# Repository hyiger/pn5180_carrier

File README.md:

# PN5180 8-Bay NFC Reader Carrier

Carrier board that lets 4 or 8 PN5180 breakout modules plug in over ~30 cm cables with
Molex CLIK-Mate 1.50 mm dual-row (2×5) positive-lock connectors (CLIK-Mate is the white
latching family used on the Prusa LoveBoard) and share one SPI bus with a Seeed Studio
XIAO ESP32C6 soldered flat at the top centre of the board. It runs from the printer's 24 V supply through an MP1584EN buck
module soldered flat onto the carrier. Every part is SMD except the buck module's four
through-hole pads; the XIAO is soldered flat by its castellations. A 74HC138 decodes
3 address lines into the 8 chip selects; a 74HC151 muxes the 8 BUSY lines back to a
single GPIO. The PN5180's IRQ pin is not used — BUSY is the only handshake the SPI
protocol needs.

**GPIO cost: 9 of the XIAO's 11 pins** — SCK, MOSI, MISO, A0, A1, A2, /EN, BUSY, /RST.
D6 and D7 are spare.

Author: hyiger · Rev 1.4 · KiCad 10 files (saved with 10.0.6; KiCad 9 and older cannot open them)

## Files

| File | Purpose |
|---|---|
| `pn5180_carrier.kicad_pro` | Project file — open this in KiCad 10 |
| `pn5180_carrier.kicad_sch` | Schematic (single A3 sheet, all symbols embedded) |
| `pn5180_carrier.kicad_pcb` | 2-layer PCB, 62.5 × 106.5 mm. Layout in progress: J1–J8 now carry the 2×5 503148-1090 footprints (swapped 2026-09-05) but their tracks still need re-routing; a few other nets unrouted; mounting holes not yet placed. All 35 footprints reference a 3D model |
| `carrier.kicad_sym` + `sym-lib-table` | Project-local symbol library (same symbols, for editing) |
| `carrier.pretty/` + `fp-lib-table` | Project-local footprints: the XIAO castellated SMD pattern (plus the older 2×7-socket version, geometry from Seeed's OPL library), the MP1584EN module pads, the CLIK-Mate 503148-1090 2×5 receptacle (from Molex's catalog drawing — KiCad ships no dual-row CLIK-Mate footprint), and copies of the stock 502494-0270 (J10) and NANO2 (F1) footprints that differ only in pointing at a project 3D model |
| `pn5180_carrier_schematic.pdf` / `.png` | Rendered schematic, no KiCad needed |
| `pn5180_carrier_bom.csv` | Full BOM: refs, qty, MPN, Mouser #, footprint, DNP flag |
| `pn5180_carrier_mouser_order.csv` | One-board order list for Mouser's BOM tool (populated parts and cable-side parts with spare terminals) |
| `gerbers/`, `gerbers.zip` | Preview gerber/drill export of the unfinished layout, still with the 1×10 connectors — not a fab package |
| `check_netlist.py` | Asserts the exported netlist against the intended connectivity (`kicad-cli sch export netlist --format kicadsexpr -o net.txt pn5180_carrier.kicad_sch`, then `python3 check_netlist.py net.txt`) |
| `gen_kicad.py` | Historical generator that produced the schematic, symbol library, footprints and BOM through rev 1.3 (KiCad 7 format). The KiCad files have been hand-edited since and are authoritative — don't re-run it over them |
| `CLAUDE.md`, `MEMORY.md` | Design guide and decision log: verified part data, layout state, ERC/DRC baseline, open items |
| `.gitignore` | Keeps KiCad's transient files (`.history/`, `.kicad_prl`, lock files), kicad-cli check outputs and `renders/` out of git |
| `carrier.3dshapes/` | Simplified VRML 3D models (boxes with the right envelopes and colours) for the parts KiCad ships no model for: the 2×5 and 1×2 CLIK-Mate receptacles, the XIAO (flat, plus a socketed variant), the MP1584EN module (black no-trimmer type), the NANO2 fuse. Generated by `tools/gen_3d_models.py`; drop in vendor STEP files when you have them |
| `tools/` | `gen_clikmate_2x5_fp.py` (the 503148-1090 footprint), `gen_xiao_smd_fp.py` (the XIAO castellated footprint), `gen_3d_models.py` (the models above), `render_3d_preview.py` (top, isometric and close-up PNGs of the board via `kicad-cli pcb render`; run with KiCad's bundled Python) |
| `pn5180_carrier_3d_preview.png` | Rendered 3D view of the board with those models |

Footprints reference the stock KiCad libraries and every name was verified against
the 10.0 library set (`Capacitor_SMD`, `Diode_SMD`, `Package_SO`, `Resistor_SMD`, …). If a newer
library renames one, reassign it in the footprint tool — nothing in the netlist
depends on the footprint. Command-line checks use KiCad's `kicad-cli`: `sch erc`,
`pcb drc --schematic-parity`, and `sch export netlist` followed by `check_netlist.py`.

## Connector pinouts

### J1–J8: bay connectors (Molex 503148-1090, CLIK-Mate 1.50 mm 2×5 dual-row right-angle SMT)

Build cables by Molex circuit number: cavity *n* of the 503149-1000 housing is signal *n*,
and signals 1–9 follow the first nine positions of the common red PN5180 module's header,
so the module end is a straight 1-to-9 run plus the second GND (cavity 10 into the same
module GND as cavity 9). Molex's catalog drawings number the two rows as stacked pairs —
odd circuits (1, 3, 5, 7, 9) in one row, even (2, 4, 6, 8, 10) in the other — which puts
5V over 3V3, /RST over NSS, MOSI over MISO, SCK over BUSY and the two GNDs in the last
column. That pairing and the receptacle's lead order are read off the drawings rather than
dimensioned, so before crimping the first cable confirm on Molex's 503149/503148 sales
drawings which end is circuit 1 (and from which face the drawing looks), which row carries
the odd circuits, and the 502579 terminal's insertion orientation. On the PCB the
receptacle's ten leads come out in one 0.75 mm-pitch line, numbered 1 to 10 from the pin-1
end (chamfer and triangle on the footprint), offset half a pitch toward pin 10 because the
even-row tails jog sideways. Pin 10 is a second GND: run it as a separate wire twisted with
SCK and crimp both returns into the module's GND at the far end, which tightens the SCK
return loop over the 30 cm. Verify the module's header order before building cables.

| Pin | Signal | Notes |
|---|---|---|
| 1 | 5V | From carrier 5V rail (module TVDD / RF power) |
| 2 | 3V3 | From the carrier LDO (U4), direct |
| 3 | /RST | Shared by all bays |
| 4 | NSS | Bay-specific, from 74HC138 output *n* |
| 5 | MOSI | Shared |
| 6 | MISO | Shared (module tri-states when NSS high) |
| 7 | SCK | Shared |
| 8 | BUSY | Bay-specific, to 74HC151 input *n*, 100k pull-down (RN1/RN2) |
| 9 | GND | |
| 10 | GND | Second return — twist with SCK in the harness |

Bay *n* ↔ J(n+1) ↔ 74HC138 Y*n* ↔ 74HC151 D*n*. Bay 0 is address 000, bay 7 is 111.

Most PN5180 modules expect both 5 V and 3.3 V supplied (3.3 V for VBAT/PVDD, 5 V for the
RF stage), so the carrier feeds both. If your modules regulate 3.3 V onboard and drive
that pin as an *output*, leave pin 2 out of the cable rather than paralleling two LDOs.

### U5: Seeed XIAO ESP32C6, soldered flat on castellated pads

Pin numbers follow Seeed's own symbol/footprint: 1–11 = D0–D10, 12 = 3V3 out, 13 = GND,
14 = 5V (USB VBUS). Pins 1 (D0) and 14 (5V) are at the USB end. The footprint
(`carrier:Seeed_XIAO_ESP32C6_SMD`) puts 14 SMD pads of 1.5 × 2.5 mm under the module's
castellations (2.54 mm pitch, rows 17.8 mm apart, extending 1.25 mm past the module edge
for the fillet) and carries the 21 × 17.8 mm outline, the USB-C overhang and an antenna
marker — place the XIAO with the USB end at the carrier's top edge and the antenna end
inboard, and keep copper off both layers under the antenna end. The socketed alternative
(`Seeed_XIAO_2x7_Socket`, two Würth 61300711821 1×7 headers) stays in the library.

| Signal | XIAO pin | Symbol pin | GPIO* | Note |
|---|---|---|---|---|
| SCK | D8 | 9 | 19 | hardware SPI SCK, via R6 33 Ω |
| MISO | D9 | 10 | 20 | hardware SPI MISO |
| MOSI | D10 | 11 | 18 | hardware SPI MOSI, via R7 33 Ω |
| /EN | D3 | 4 | 21 | → 74HC138 /E1 (acts as NSS) |
| A0 | D0 | 1 | 0 | |
| A1 | D1 | 2 | 1 | |
| A2 | D2 | 3 | 2 | |
| BUSY | D4 | 5 | 22 | 74HC151 output (I²C SDA pin, unused as such) |
| /RST | D5 | 6 | 23 | shared reset to all bays |
| spare | D6 | 7 | 16 | NC (UART0 TX) |
| spare | D7 | 8 | 17 | NC (UART0 RX) |
| 3V3 out | — | 12 | | NC — the carrier has its own 3V3 LDO |
| GND | — | 13 | | |
| 5V | — | 14 | | from carrier 5V through D1 |

\* GPIO numbers per Seeed's pin diagram; write firmware with the `D0…D10` names from the
board's `pins_arduino.h` and they can't be wrong. `SPI.begin()` with no arguments uses
D8/D9/D10.

**Power path:** Seeed states the XIAO's 5V pin is the raw USB VBUS and that an external
supply must go through a diode. D1 (PMEG2010AEH, 0.3 V drop at our current) does that, so
USB can stay plugged in for flashing while the carrier is powered — neither source can
push into the other. The XIAO's own LDO makes its 3.3 V from ~4.7 V; that's fine. With the
carrier unpowered, USB alone runs the XIAO and D1 keeps VBUS out of the carrier's 5 V rail.

### J10: 24 V input (Molex 502494-0270, CLIK-Mate 2.00 mm 1×2 right-angle SMT)

| Pin | Signal |
|---|---|
| 1 | +24 V from the printer PSU |
| 2 | GND (printer PSU return) |

**Tapping the Core One.** Take it from the PSU's 24 V output terminals — put a crimped
fork/spade terminal under the existing screw next to the xBuddy's lead, positive and
return together, 22 AWG is plenty. Check polarity with a meter before you plug the
carrier in; the connector is keyed but the PSU end isn't. Load is ≤ ~0.4 A at 24 V worst
case (the module's 1.5 A limit at 5 V), typically well under that, so the PSU's headroom
is not a concern. The xBuddy's MMU port also carries firmware-switched 24 V, but it's only
enabled when an MMU is configured, so the PSU terminals are the practical tap.

**Input stage (all on the carrier):** F1 1 A (NANO2 451/453, fast-acting — see open item 13) → D2 SMAJ28A TVS (clamps motor
regen spikes; a reversed input forward-biases it and blows F1) → D3 PMEG6030EP reverse
Schottky (keeps the reversed input off C8/C9 and the module; F1 still blows through D2,
so replace it after fixing the miswire) → C8/C9 2 × 10 µF 50 V → U6.

**Buck (U6): MP1584EN mini module, mounted flat.** The footprint has four 3 mm
through-hole pads on the module's 18.54 × 8.13 mm pad rectangle; lay the module on the
carrier and solder down through its own plated holes, or stand it on four header-pin
stubs — both work on the same pads. IN pads at the "IN" silk end, OUT at "OUT", "+" marks
the top row. Module pad labels vary between makers, so check the module's own silkscreen
against the footprint before soldering.

Three things about this module on a 24 V rail:

- It's rated 28 V max. The TVS (28 V standoff, clamping from ~31 V) and C8/C9 are what
  keep spikes off it — don't leave them out to save parts.
- It's the **fixed 5 V output** variant (black PCB, no trimmer — the one modelled in
  3D). Don't substitute the adjustable type: a bumped pot can put up to 20 V into the
  readers and the XIAO. Check 5.0 V at OUT+ on the bench before fitting the readers.
- The seller's own guidance is 1.5 A continuous without a heatsink. The carrier's real
  draw is well under 1 A (one RF field at a time), so that's fine; give it some copper
  under the pads anyway.

### Cables (~30 cm)

Bay cable: 503149-1000 dual-row housing at the carrier with 10 × 502579 terminals on
24–28 AWG stranded wire — the terminal takes insulation of 0.78–1.28 mm OD, so use
thin-wall UL1061/UL1571-type wire and check the specific wire's maximum OD against 1.28 mm
(common UL1007 24 AWG at ~1.5 mm is too fat, and some UL1061 24 AWG is specified at
1.3 mm); 24 AWG for 5V/GND is plenty at ≤ 0.25 A per bay — and a 2.54 mm DuPont-style
female on the module end (or solder to the module header). Power: the 24 V cable stays on the 2.00 mm family, 502439-0200 housing
with 502438 terminals on 22 AWG. The XIAO is soldered to the carrier, so bay and power
cables are the only cables.

The housing latches inside the receptacle (the CLIK; one inner lock on the 10-circuit
housing) and releases with a squeeze — no tools. Molex's hand crimpers are expensive
(distributor listings name 200218-7400 for the 1.50 mm 502579 and 63819-2800 for the
2.00 mm 502438 — not checked against Molex's tooling spec); both are small open-barrel
terminals and a small-barrel ratchet crimper (Engineer PA-09 or an IWISS SN-01BM-class
tool) does the job — pull-test the first few crimps, because with 24–28 AWG in a 1.5 mm
terminal the tool is what makes or breaks a cable. Molex also sells pre-crimped CLIK-Mate 1.50 leads
(79758-1011: 300 mm, 24 AWG UL1061, terminal on both ends, packs of 10 at RS) — cut one
end off and solder it to the module header if you'd rather skip crimping.

Eight 30 cm unterminated stubs hanging off one SPI bus is a real transmission-line load,
so the design takes three precautions:

- **R6/R7 (33 Ω) in series with SCK and MOSI**, a few mm from the XIAO's SCK/MOSI pads and
  before the bus fans out — proper source termination for the star, taking the edge off
  the ESP32's ~2 ns rise times. Fit 0 Ω if you scope it and it's clean; 47–68 Ω if you
  see ringing.
- **SPI clock ≤ 1 MHz.** The PN5180 doesn't need more for inventory polling, and a 1 µs
  bit period gives the reflections on a 30 cm stub (a few ns round trip) time to settle.
- **Lowest ESP32 drive strength that works:** `gpio_set_drive_capability((gpio_num_t)D8,
  GPIO_DRIVE_CAP_0)` (and `D10` for MOSI) slows the edges further.

Route GND wires as close to SCK as the harness allows. MISO is driven by the PN5180 (slower
edges) and needs nothing extra. NSS/BUSY see one stub each and are fine.

## How the selection logic works

- `A0..A2` → 74HC138 address inputs **and** both 74HC151 select inputs.
- `/EN` → 74HC138 `/E1` (G2A). Low = the addressed bay's NSS goes low; high = every NSS high.
  Wire the library's "NSS" pin to `/EN` and it just works — the library toggles NSS,
  the decoder routes it.
- `BUSY` (XIAO D4, symbol pin 5) is the 74HC151 output = the BUSY of the addressed bay. Wire
  it to the library's "BUSY" pin.
- `/E2` is grounded, `E3` tied high; 74HC151 `/E` grounded (always enabled).
- R6/R7 sit between the ESP32 and the SCK/MOSI bus (nets `SCK_IN`/`MOSI_IN` on the ESP32 side).
- Pull-ups on `/EN` and `/RST` and pull-downs on `A0..A2` define everything while the
  ESP32 is booting or unplugged. The 4×100k arrays RN1/RN2 keep unfitted bays' BUSY
  inputs from floating. Bay *n* uses element (*n* mod 4)+1 of RN(1 + *n*÷4): pin
  (*n* mod 4)+1 to the signal and its opposite pin (8, 7, 6, 5) to GND — the standard
  1–8/2–7/3–6/4–5 pairing.

**Rule:** change `A0..A2` only while `/EN` is high, or two NSS lines can glitch low
during the decoder transition.

## Firmware sketch (ATrappmann PN5180 library)

```cpp
// Seeed XIAO ESP32C6 soldered to the carrier (Arduino-ESP32 core 3.x, board "XIAO_ESP32C6")
#define PIN_A0   D0
#define PIN_A1   D1
#define PIN_A2   D2
#define PIN_EN   D3     // -> 74HC138 /E1, acts as "NSS" for the addressed bay
#define PIN_BUSY D4     // <- 74HC151 Y
#define PIN_RST  D5
#define BAYS      8     // 4 for a half-populated board
// SCK D8 / MISO D9 / MOSI D10 are the board's hardware SPI pins

PN5180ISO15693 nfc(PIN_EN, PIN_BUSY, PIN_RST);   // one instance for all bays

void selectBay(uint8_t n) {
  digitalWrite(PIN_EN, HIGH);            // deselect everything before changing address
  digitalWrite(PIN_A0, n & 1);
  digitalWrite(PIN_A1, (n >> 1) & 1);
  digitalWrite(PIN_A2, (n >> 2) & 1);
}

void setup() {
  pinMode(PIN_A0, OUTPUT); pinMode(PIN_A1, OUTPUT); pinMode(PIN_A2, OUTPUT);
  pinMode(PIN_EN, OUTPUT); digitalWrite(PIN_EN, HIGH);
  nfc.begin();                           // SPI on D8/D9/D10; keep the SPI clock <= 1 MHz
  gpio_set_drive_capability((gpio_num_t)D8,  GPIO_DRIVE_CAP_0);   // soften SCK/MOSI edges
  gpio_set_drive_capability((gpio_num_t)D10, GPIO_DRIVE_CAP_0);
  // shared /RST: pulse once, then finish the post-reset handshake per bay
  digitalWrite(PIN_RST, LOW);  delay(10);
  digitalWrite(PIN_RST, HIGH); delay(10);
  for (uint8_t b = 0; b < BAYS; b++) {
    selectBay(b);
    while (!(nfc.getIRQStatus() & IDLE_IRQ_STAT)) {}   // add a timeout in real code
    nfc.clearIRQStatus(0xFFFFFFFF);
  }
}

void loop() {
  for (uint8_t b = 0; b < BAYS; b++) {
    selectBay(b);
    nfc.setupRF();                       // RF on, this bay only
    uint8_t uid[8];
    bool present = (nfc.getInventory(uid) == ISO15693_EC_OK);
    nfc.setRF_off();                     // field off before moving to the next bay
    updateBay(b, present, uid);          // debounce: 2-3 misses before "removed"
  }
}
```

The stock library's `while (digitalRead(BUSY))` loops have no timeout; add one
(a few ms) so an empty bay or a wedged module can't hang the sweep.

## Layout notes

The 2-layer PCB in `pn5180_carrier.kicad_pcb` follows these rules; the current routing
state and the ERC/DRC baseline are tracked in `MEMORY.md`.

- Ground plane on one layer; SPI signals short, routed as a star or short daisy chain
  from U5 to the bay connectors. With 8 loads plus cable capacitance, ≤ 1 MHz SPI.
- U5 at the top centre, USB-C end at the top board edge (the rule is a 1–2 mm overhang;
  as placed the module edge sits 0.5 mm inside and only the USB-C shell is 1.05 mm proud),
  antenna end (opposite the USB) pointing inboard with
  a copper keep-out on both layers under it. The XIAO is soldered flat by its
  castellations (no sockets); it also has an external-antenna u.FL if the rack's metal
  gets in the way.
- Bay connectors down both long edges (J5–J8 left, J1–J4 right), in bay order, so cables
  don't cross. The 503148 receptacles are SMT: ten 0.55 mm signal pads at 0.75 mm pitch
  in one line at the rear (reflow, or drag-solder with plenty of flux) and two solder-nail
  pads ("MP" in the footprint) at the front corners — the nails, not the signal pins, take
  the cable-pull load, so give them full paste and don't thin the copper under them.
  Right-angle parts: the cable leaves flat along the board plane. The 2×5 body is 11.8 mm
  long against the old 1×10's 24.0 mm, so the connector columns can tighten up. **J1–J8
  were swapped to the 2×5 footprint on 2026-09-05** (same positions and orientations,
  nail pads outboard); their tracks still have to be re-routed, then refill zones, run
  DRC and regenerate the gerbers (CLAUDE.md open item 12).
- R6/R7 within a few mm of U5 pins 9/11 (D8 SCK / D10 MOSI), before the traces fan out.
- U1/U2 near U5 (short A0–A2, /EN, BUSY traces); the eight NSS/BUSY lines then run out
  to the connector edge.
- U6 module: C8/C9 right at its IN pads, a solid GND pour under it, and keep it away from
  the SPI lines and the XIAO's antenna (it switches at ~1.5 MHz with a small inductor).
- F1/D2/D3 near J10; C6/C7 and C4 near U4; C1/C2 within a few mm of their IC VCC pins.
- U4 (SOT-223) with a copper pour on the tab (tab = OUTPUT, part of the 3V3 net); at ~200 mA on 3V3 it dissipates ~0.35 W.
- M3 mounting holes are still to be added (not in the schematic).
- For a 4-bay build simply leave J5–J8 (and RN2) unpopulated. Firmware `BAYS = 4`.

## BOM (all SMD except U6's four pads)

Rev 1.4. Every symbol in the schematic carries `Manufacturer`, `MPN` and `Mouser` fields,
so KiCad's own BOM export reproduces this table. `pn5180_carrier_mouser_order.csv` can be
uploaded directly to Mouser's BOM tool.

| Ref | Qty | Part | Mouser # | Footprint |
|---|---|---|---|---|
| U1 | 1 | TI SN74HC138DR | 595-SN74HC138DR | Package_SO:SOIC-16_3.9x9.9mm_P1.27mm |
| U2 | 1 | TI SN74HC151DR | 595-SN74HC151DR | Package_SO:SOIC-16_3.9x9.9mm_P1.27mm |
| U4 | 1 | TI TLV1117LV33DCYR, 3.3 V 1 A ceramic-stable LDO | 595-TLV1117LV33DCYR | Package_TO_SOT_SMD:SOT-223-3_TabPin2 |
| J1–J8 | 8 | Molex 503148-1090, CLIK-Mate 1.50 mm dual-row RA SMT receptacle 2×5 (1 A/contact) | 538-503148-1090 | carrier:Molex_CLIK-Mate_503148-1090_2x05-1MP_P1.50mm_Horizontal |
| U5 | 1 | Seeed Studio XIAO ESP32C6 (SKU 113991182) — user-supplied, soldered flat | 713-113991182 (verify) | carrier:Seeed_XIAO_ESP32C6_SMD |
| D1 | 1 | Nexperia PMEG2010AEH, Schottky 20 V 1 A, SOD-123 | 771-PMEG2010AEH | Diode_SMD:D_SOD-123 |
| J10 | 1 | Molex 502494-0270, CLIK-Mate 2.00 mm RA SMT receptacle 1×2 (24 V in) | 538-502494-0270 | carrier:Molex_CLIK-Mate_502494-0270_1x02-1MP_P2.00mm_Horizontal (local copy of the stock footprint, with 3D model) |
| U6 | 1 | MP1584EN mini buck module, 22 × 17 mm, fixed 5 V output (no trimmer) — user-supplied (Amazon) | — | carrier:MP1584EN_Module_22x17 |
| F1 | 1 | Littelfuse 0453001.MR, 1 A, NANO2 (451/453 is the fast-acting series — see open item 13) | 576-0453001.MR | carrier:Fuse_Littelfuse-NANO2-451_453 (local copy of the stock footprint, with 3D model) |
| D2 | 1 | Littelfuse SMAJ28A TVS, 28 V standoff, SMA | 576-SMAJ28A | Diode_SMD:D_SMA |
| D3 | 1 | Nexperia PMEG6030EP Schottky 60 V 3 A (reverse polarity) | 771-PMEG6030EP | Diode_SMD:D_SOD-128 |
| C8, C9 | 2 | Murata GRM32ER71H106KA12L, 10 µF 50 V X7R 1210 | 81-GRM32ER71H106KA12L | Capacitor_SMD:C_1210_3225Metric_Pad1.33x2.70mm_HandSolder |
| R1–R5 | 5 | Yageo RC0603FR-0710KL, 10k 1% 0603 | 603-RC0603FR-0710KL | Resistor_SMD:R_0603_1608Metric_Pad0.98x0.95mm_HandSolder |
| R6, R7 | 2 | Yageo RC0603FR-0733RL, 33 Ω 1% 0603 (SCK/MOSI series) | 603-RC0603FR-0733RL | Resistor_SMD:R_0603_1608Metric_Pad0.98x0.95mm_HandSolder |
| RN1, RN2 | 2 | Yageo YC164-FR-07100KL, 4×100k 1% isolated array | 603-YC164-FR-07100KL | Resistor_SMD:R_Array_Convex_4x0603 |
| C1, C2 | 2 | Murata GRM188R71H104KA93D, 100 nF 50 V X7R 0603 | 81-GRM188R71H104KA93D | Capacitor_SMD:C_0603_1608Metric_Pad1.08x0.95mm_HandSolder |
| C4 | 1 | Murata GRM188R61A106KE69D, 10 µF 10 V X5R 0603 | 81-GRM188R61A106KE69D | Capacitor_SMD:C_0603_1608Metric_Pad1.08x0.95mm_HandSolder |
| C5 | 1 | Murata GRM188R60J226MEA0D, 22 µF 6.3 V X5R 0603 | 81-GRM188R60J226MEA0D | Capacitor_SMD:C_0603_1608Metric_Pad1.08x0.95mm_HandSolder |
| C6 | 1 | Taiyo Yuden MSASJ32MAB5227MPNDT1, 220 µF 6.3 V X5R 1210 | 963-MSASJ32MAB5227MP | Capacitor_SMD:C_1210_3225Metric_Pad1.33x2.70mm_HandSolder |
| C7 | 1 | Same — **DNP**, parallel pads for extra bulk | 963-MSASJ32MAB5227MP | Capacitor_SMD:C_1210_3225Metric_Pad1.33x2.70mm_HandSolder |

Cable side:

| Part | Mouser # | Qty / board | Use |
|---|---|---|---|
| Molex 503149-1000 CLIK-Mate 1.50 dual-row positive-lock plug housing 2×5 | 538-503149-1000 | 8 | Bay cables |
| Molex 502579-0000 CLIK-Mate 1.50 crimp terminal, 24–28 AWG, cut strip of 100 | 538-502579-0000-CT | 100 (80 needed) | Bay cables |
| Molex 502439-0200 CLIK-Mate 2.00 positive-lock housing 1×2 | 538-502439-0200 | 1 | 24 V cable |
| Molex 502438-0100 CLIK-Mate 2.00 crimp terminal, loose, 22–26 AWG | 538-502438-0100 | 2 (+spares) | 24 V cable |

Stock check on Mouser, 2026-09-04/05: 503148-1090 1,696 in stock, minimum 1, $1.98 at 10;
503149-1000 7,865, minimum 1, $0.44 at 10; 502579-0000 cut strip 33,700, minimum 100,
$5.70 per 100. An aggregator snapshot the same day showed the receptacle at DigiKey
(11,852, minimum 1), Newark (63, minimum 1) and Arrow (6,046), and the housing at Newark
(6,475, minimum 10); no obsolescence notice on any of these parts.
The finer 503429-0000 terminal (26–30 AWG) is reel-only (20,000) — don't spec it. The
vertical (top-entry) dual-row receptacle is 503154-1090 (2 A/contact, a two-row land
pattern); the right-angle part used here is rated 1.0 A per contact, 30 mating cycles — a
bay draws ≤ 0.25 A.

Mouser numbers follow Mouser's manufacturer-prefix + MPN scheme (595 = TI, 538 = Molex,
603 = Yageo, 81 = Murata, 710 = Würth, 771 = Nexperia, 713 = Seeed, 576 = Littelfuse). 963-MSASJ32MAB5227MP was read from the product page; the
others follow the scheme. Double-check stock and packaging (cut tape vs. reel) at checkout.

Capacitor notes:

- C6 is a 6.3 V X5R part on the 5 V rail. That's inside its rating, but class-2 ceramics
  lose capacitance under DC bias — expect roughly a quarter of its nominal 220 µF at
  5 V. Together with the MP1584EN module's own output capacitor that's plenty for the
  ~250 mA RF-on step; C7 gives you a second set of pads if the rail shows sag when a
  bay's field switches on.
- U4 is a TLV1117LV33, designed for ceramic output capacitors (TI specifies ≥ 10 µF,
  any ESR, stable at 0 mA load). C5's 22 µF 0603 is worth roughly 10–12 µF after
  DC-bias derating at 3.3 V, which meets that minimum; for more margin use a 22 µF in
  0805 or two 0603s in parallel. Don't substitute a classic AMS1117/TLV1117 here
  without changing C5 to a tantalum — those parts need output ESR to stay stable.
- TLV1117LV limits: Vin ≤ 5.5 V (6 V absolute). Fine on a regulated 5 V rail, but never
  feed J10 from an unregulated "5 V" adapter that idles at 6–7 V. Dropout is ~0.45 V at
  1 A, so 3V3 holds up even if the input droops to 4 V.

## Going to 16 bays

Swap U1 for a 74HC154 (4-to-16), add a second 74HC151 selected by A3 and two more
arrays: 6 select GPIOs, 10 of the XIAO's 11 pins with SPI and /RST. The ESP32-C6 has one
user SPI host, so 16 stubs stay on one bus — keep it at ≤ 1 MHz with the source
termination, or move to an MCU with a second SPI port.

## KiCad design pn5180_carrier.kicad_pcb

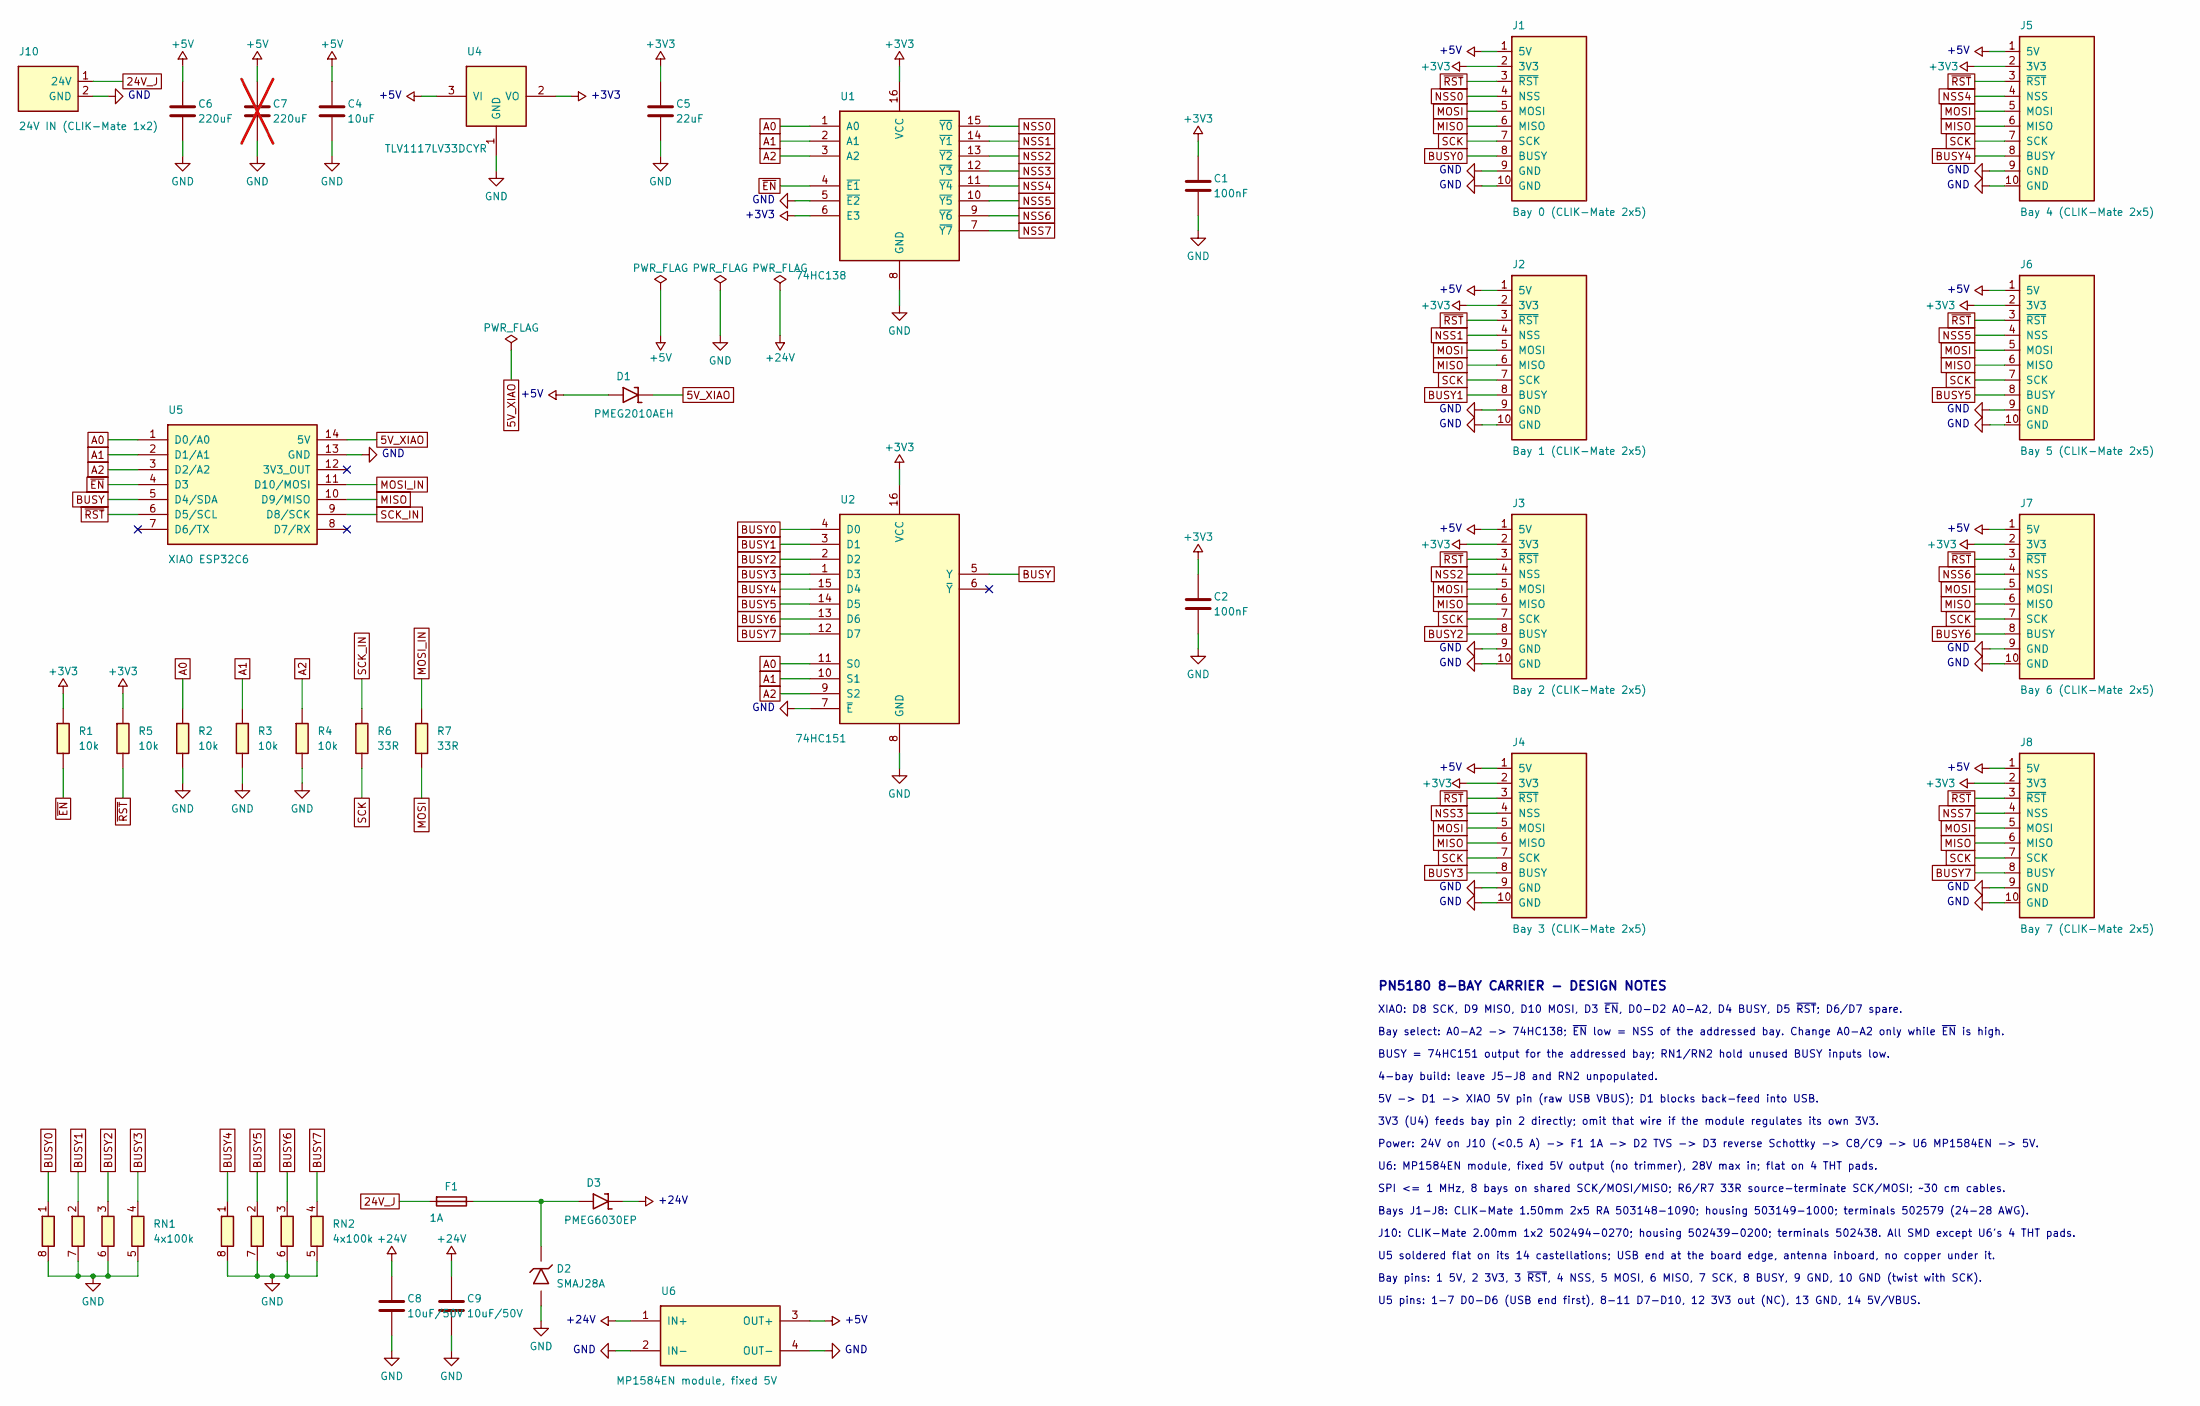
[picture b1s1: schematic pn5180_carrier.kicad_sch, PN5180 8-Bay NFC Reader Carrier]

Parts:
C1, C2: 100nF; C_0603_1608Metric_Pad1.08x0.95mm_HandSolder; MPN GRM188R71H104KA93D; Mouser 81-GRM188R71H104KA93D
C4: 10uF; C_0603_1608Metric_Pad1.08x0.95mm_HandSolder; MPN GRM188R61A106KE69D; Mouser 81-GRM188R61A106KE69D
C5: 22uF; C_0603_1608Metric_Pad1.08x0.95mm_HandSolder; MPN GRM188R60J226MEA0D; Mouser 81-GRM188R60J226MEA0D
C6: 220uF; C_1210_3225Metric_Pad1.33x2.70mm_HandSolder; MPN MSASJ32MAB5227MPNDT1; Mouser 963-MSASJ32MAB5227MP
C7: 220uF; C_1210_3225Metric_Pad1.33x2.70mm_HandSolder; MPN MSASJ32MAB5227MPNDT1; Mouser 963-MSASJ32MAB5227MP; not fitted
C8, C9: 10uF/50V; C_1210_3225Metric_Pad1.33x2.70mm_HandSolder; MPN GRM32ER71H106KA12L; Mouser 81-GRM32ER71H106KA12L
D1: PMEG2010AEH; D_SOD-123; MPN PMEG2010AEH; Mouser 771-PMEG2010AEH
D2: SMAJ28A; D_SMA; MPN SMAJ28A; Mouser 576-SMAJ28A
D3: PMEG6030EP; D_SOD-128; MPN PMEG6030EP; Mouser 771-PMEG6030EP
F1: 1A; Fuse_Littelfuse-NANO2-451_453; MPN 0453001.MR; Mouser 576-0453001.MR
J1: Bay 0 (CLIK-Mate 2x5); Molex_CLIK-Mate_503148-1090_2x05-1MP_P1.50mm_Horizontal; MPN 503148-1090; Mouser 538-503148-1090
J2: Bay 1 (CLIK-Mate 2x5); Molex_CLIK-Mate_503148-1090_2x05-1MP_P1.50mm_Horizontal; MPN 503148-1090; Mouser 538-503148-1090
J3: Bay 2 (CLIK-Mate 2x5); Molex_CLIK-Mate_503148-1090_2x05-1MP_P1.50mm_Horizontal; MPN 503148-1090; Mouser 538-503148-1090
J4: Bay 3 (CLIK-Mate 2x5); Molex_CLIK-Mate_503148-1090_2x05-1MP_P1.50mm_Horizontal; MPN 503148-1090; Mouser 538-503148-1090
J5: Bay 4 (CLIK-Mate 2x5); Molex_CLIK-Mate_503148-1090_2x05-1MP_P1.50mm_Horizontal; MPN 503148-1090; Mouser 538-503148-1090
J6: Bay 5 (CLIK-Mate 2x5); Molex_CLIK-Mate_503148-1090_2x05-1MP_P1.50mm_Horizontal; MPN 503148-1090; Mouser 538-503148-1090
J7: Bay 6 (CLIK-Mate 2x5); Molex_CLIK-Mate_503148-1090_2x05-1MP_P1.50mm_Horizontal; MPN 503148-1090; Mouser 538-503148-1090
J8: Bay 7 (CLIK-Mate 2x5); Molex_CLIK-Mate_503148-1090_2x05-1MP_P1.50mm_Horizontal; MPN 503148-1090; Mouser 538-503148-1090
J10: 24V IN (CLIK-Mate 1x2); Molex_CLIK-Mate_502494-0270_1x02-1MP_P2.00mm_Horizontal; MPN 502494-0270; Mouser 538-502494-0270
R1, R2, R3, R4, R5: 10k; R_0603_1608Metric_Pad0.98x0.95mm_HandSolder; MPN RC0603FR-0710KL; Mouser 603-RC0603FR-0710KL
R6, R7: 33R; R_0603_1608Metric_Pad0.98x0.95mm_HandSolder; MPN RC0603FR-0733RL; Mouser 603-RC0603FR-0733RL
RN1, RN2: 4x100k; R_Array_Convex_4x0603; MPN YC164-FR-07100KL; Mouser 603-YC164-FR-07100KL
U1: 74HC138; SOIC-16_3.9x9.9mm_P1.27mm; MPN SN74HC138DR; Mouser 595-SN74HC138DR
U2: 74HC151; SOIC-16_3.9x9.9mm_P1.27mm; MPN SN74HC151DR; Mouser 595-SN74HC151DR
U4: TLV1117LV33DCYR; SOT-223-3_TabPin2; MPN TLV1117LV33DCYR; Mouser 595-TLV1117LV33DCYR
U5: XIAO ESP32C6; Seeed_XIAO_ESP32C6_SMD; MPN XIAO ESP32C6; Mouser 713-113991182
U6: MP1584EN module, fixed 5V; MP1584EN_Module_22x17; MPN MP1584EN mini buck module

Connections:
5V_XIAO: D1.1 (K), U5.14 (5V)
24V_J: F1.1, J10.1 (24V)
+3V3: C1.1, C2.1, C5.1, J1.2 (3V3), J2.2 (3V3), J3.2 (3V3), J4.2 (3V3), J5.2 (3V3), J6.2 (3V3), J7.2 (3V3), J8.2 (3V3), R1.1, R5.1, U1.6 (E3), U1.16 (VCC), U2.16 (VCC), U4.2 (VO)
+5V: C4.1, C6.1, C7.1, D1.2 (A), J1.1 (5V), J2.1 (5V), J3.1 (5V), J4.1 (5V), J5.1 (5V), J6.1 (5V), J7.1 (5V), J8.1 (5V), U4.3 (VI), U6.3 (OUT+)
+24V: C8.1, C9.1, D3.1 (K), U6.1 (IN+)
A0: R2.1, U1.1 (A0), U2.11 (S0), U5.1 (D0/A0)
A1: R3.1, U1.2 (A1), U2.10 (S1), U5.2 (D1/A1)
A2: R4.1, U1.3 (A2), U2.9 (S2), U5.3 (D2/A2)
BUSY: U2.5 (Y), U5.5 (D4/SDA)
BUSY0: J1.8 (BUSY), RN1.1 (R1.1), U2.4 (D0)
BUSY1: J2.8 (BUSY), RN1.2 (R2.1), U2.3 (D1)
BUSY2: J3.8 (BUSY), RN1.3 (R3.1), U2.2 (D2)
BUSY3: J4.8 (BUSY), RN1.4 (R4.1), U2.1 (D3)
BUSY4: J5.8 (BUSY), RN2.1 (R1.1), U2.15 (D4)
BUSY5: J6.8 (BUSY), RN2.2 (R2.1), U2.14 (D5)
BUSY6: J7.8 (BUSY), RN2.3 (R3.1), U2.13 (D6)
BUSY7: J8.8 (BUSY), RN2.4 (R4.1), U2.12 (D7)
GND: C1.2, C2.2, C4.2, C5.2, C6.2, C7.2, C8.2, C9.2, D2.2 (A), J1.9 (GND), J1.10 (GND), J2.9 (GND), J2.10 (GND), J3.9 (GND), J3.10 (GND), J4.9 (GND), J4.10 (GND), J5.9 (GND), J5.10 (GND), J6.9 (GND), J6.10 (GND), J7.9 (GND), J7.10 (GND), J8.9 (GND), J8.10 (GND), J10.2 (GND), R2.2, R3.2, R4.2, RN1.5 (R4.2), RN1.6 (R3.2), RN1.7 (R2.2), RN1.8 (R1.2), RN2.5 (R4.2), RN2.6 (R3.2), RN2.7 (R2.2), RN2.8 (R1.2), U1.5 (~E2), U1.8 (GND), U2.7 (~E), U2.8 (GND), U4.1 (GND), U5.13 (GND), U6.2 (IN-), U6.4 (OUT-)
MISO: J1.6 (MISO), J2.6 (MISO), J3.6 (MISO), J4.6 (MISO), J5.6 (MISO), J6.6 (MISO), J7.6 (MISO), J8.6 (MISO), U5.10 (D9/MISO)
MOSI: J1.5 (MOSI), J2.5 (MOSI), J3.5 (MOSI), J4.5 (MOSI), J5.5 (MOSI), J6.5 (MOSI), J7.5 (MOSI), J8.5 (MOSI), R7.2
MOSI_IN: R7.1, U5.11 (D10/MOSI)
NSS0: J1.4 (NSS), U1.15 (~Y0)
NSS1: J2.4 (NSS), U1.14 (~Y1)
NSS2: J3.4 (NSS), U1.13 (~Y2)
NSS3: J4.4 (NSS), U1.12 (~Y3)
NSS4: J5.4 (NSS), U1.11 (~Y4)
NSS5: J6.4 (NSS), U1.10 (~Y5)
NSS6: J7.4 (NSS), U1.9 (~Y6)
NSS7: J8.4 (NSS), U1.7 (~Y7)
unnamed: D2.1 (K), D3.2 (A), F1.2
SCK: J1.7 (SCK), J2.7 (SCK), J3.7 (SCK), J4.7 (SCK), J5.7 (SCK), J6.7 (SCK), J7.7 (SCK), J8.7 (SCK), R6.2
SCK_IN: R6.1, U5.9 (D8/SCK)
~EN: R1.2, U1.4 (~E1), U5.4 (D3)
~RST: J1.3 (~RST), J2.3 (~RST), J3.3 (~RST), J4.3 (~RST), J5.3 (~RST), J6.3 (~RST), J7.3 (~RST), J8.3 (~RST), R5.2, U5.6 (D5/SCL)

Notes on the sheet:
U5 soldered flat on its 14 castellations; USB end at the board edge, antenna inboard, no copper under it.
GND
+5V
4-bay build: leave J5-J8 and RN2 unpopulated.
+24V
XIAO: D8 SCK, D9 MISO, D10 MOSI, D3 ~{EN}, D0-D2 A0-A2, D4 BUSY, D5 ~{RST}; D6/D7 spare.
SPI <= 1 MHz, 8 bays on shared SCK/MOSI/MISO; R6/R7 33R source-terminate SCK/MOSI; ~30 cm cables.
5V -> D1 -> XIAO 5V pin (raw USB VBUS); D1 blocks back-feed into USB.
U6: MP1584EN module, fixed 5V output (no trimmer), 28V max in; flat on 4 THT pads.
+3V3
Bay select: A0-A2 -> 74HC138; ~{EN} low = NSS of the addressed bay. Change A0-A2 only while ~{EN} is high.
PN5180 8-BAY CARRIER - DESIGN NOTES
Bay pins: 1 5V, 2 3V3, 3 ~{RST}, 4 NSS, 5 MOSI, 6 MISO, 7 SCK, 8 BUSY, 9 GND, 10 GND (twist with SCK).
BUSY = 74HC151 output for the addressed bay; RN1/RN2 hold unused BUSY inputs low.
U5 pins: 1-7 D0-D6 (USB end first), 8-11 D7-D10, 12 3V3 out (NC), 13 GND, 14 5V/VBUS.
Power: 24V on J10 (<0.5 A) -> F1 1A -> D2 TVS -> D3 reverse Schottky -> C8/C9 -> U6 MP1584EN -> 5V.
Bays J1-J8: CLIK-Mate 1.50mm 2x5 RA 503148-1090; housing 503149-1000; terminals 502579 (24-28 AWG).
3V3 (U4) feeds bay pin 2 directly; omit that wire if the module regulates its own 3V3.
J10: CLIK-Mate 2.00mm 1x2 502494-0270; housing 502439-0200; terminals 502438. All SMD except U6's 4 THT pads.

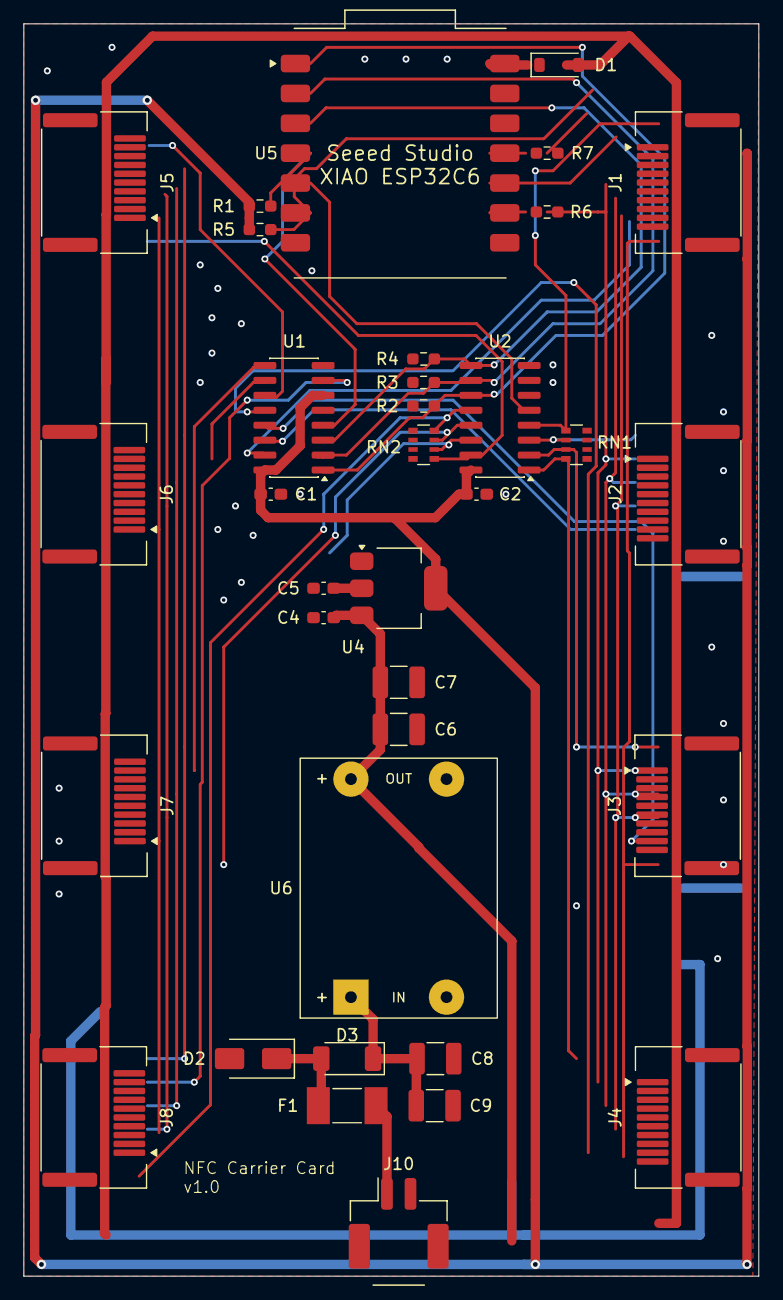
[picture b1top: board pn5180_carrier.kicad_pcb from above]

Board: 2 copper layers, 62.5 x 106.5 mm, 35 parts (0 on the bottom side), 34 nets.

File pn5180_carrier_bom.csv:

References,Qty,Value,Type,Manufacturer,MPN,Mouser Part Number,Footprint,Populate,Description
"C1, C2",2,100nF,C,Murata,GRM188R71H104KA93D,81-GRM188R71H104KA93D,Capacitor_SMD:C_0603_1608Metric_Pad1.08x0.95mm_HandSolder,,100nF 50V X7R 0603
C4,1,10uF,C,Murata,GRM188R61A106KE69D,81-GRM188R61A106KE69D,Capacitor_SMD:C_0603_1608Metric_Pad1.08x0.95mm_HandSolder,,10uF 10V X5R 0603
C5,1,22uF,C,Murata,GRM188R60J226MEA0D,81-GRM188R60J226MEA0D,Capacitor_SMD:C_0603_1608Metric_Pad1.08x0.95mm_HandSolder,,22uF 6.3V X5R 0603
C6,1,220uF,C,Taiyo Yuden,MSASJ32MAB5227MPNDT1,963-MSASJ32MAB5227MP,Capacitor_SMD:C_1210_3225Metric_Pad1.33x2.70mm_HandSolder,,220uF 6.3V X5R 1210
C7,1,220uF,C,Taiyo Yuden,MSASJ32MAB5227MPNDT1,963-MSASJ32MAB5227MP,Capacitor_SMD:C_1210_3225Metric_Pad1.33x2.70mm_HandSolder,DNP,220uF 6.3V X5R 1210
"C8, C9",2,10uF/50V,C,Murata,GRM32ER71H106KA12L,81-GRM32ER71H106KA12L,Capacitor_SMD:C_1210_3225Metric_Pad1.33x2.70mm_HandSolder,,10uF 50V X7R 1210
D1,1,PMEG2010AEH,D,Nexperia,PMEG2010AEH,771-PMEG2010AEH,Diode_SMD:D_SOD-123,,Schottky 20V 1A SOD-123
D2,1,SMAJ28A,D,Littelfuse,SMAJ28A,576-SMAJ28A,Diode_SMD:D_SMA,,"TVS 28V standoff, 400W, SMA"
D3,1,PMEG6030EP,D,Nexperia,PMEG6030EP,771-PMEG6030EP,Diode_SMD:D_SOD-128,,Schottky 60V 3A SOD-128 (reverse polarity)
F1,1,1A NANO2,F,Littelfuse,0453001.MR,576-0453001.MR,carrier:Fuse_Littelfuse-NANO2-451_453,,"1A SMD fuse, NANO2 451/453 (fast-acting series; Slo-Blo is 452/454 — see CLAUDE.md open item 13)"
"J1, J2, J3, J4, J5, J6, J7, J8",8,"CLIK-Mate 1.50mm dual-row RA SMT receptacle 2x5, positive lock",J,Molex,503148-1090,538-503148-1090,carrier:Molex_CLIK-Mate_503148-1090_2x05-1MP_P1.50mm_Horizontal,,"CLIK-Mate 1.50mm dual-row RA SMT receptacle 2x5, positive lock"
J10,1,24V IN (CLIK-Mate 1x2),J,Molex,502494-0270,538-502494-0270,carrier:Molex_CLIK-Mate_502494-0270_1x02-1MP_P2.00mm_Horizontal,,"CLIK-Mate 2.00mm RA SMT receptacle 1x2, positive lock"
"R1, R2, R3, R4, R5",5,10k,R,Yageo,RC0603FR-0710KL,603-RC0603FR-0710KL,Resistor_SMD:R_0603_1608Metric_Pad0.98x0.95mm_HandSolder,,10k 1% 0603
"R6, R7",2,33R,R,Yageo,RC0603FR-0733RL,603-RC0603FR-0733RL,Resistor_SMD:R_0603_1608Metric_Pad0.98x0.95mm_HandSolder,,33R 1% 0603
"RN1, RN2",2,4x100k,RN,Yageo,YC164-FR-07100KL,603-YC164-FR-07100KL,Resistor_SMD:R_Array_Convex_4x0603,,"4x100k 1% isolated array, 0603x4"
U1,1,74HC138,U,Texas Instruments,SN74HC138DR,595-SN74HC138DR,Package_SO:SOIC-16_3.9x9.9mm_P1.27mm,,"3-to-8 decoder, SOIC-16"
U2,1,74HC151,U,Texas Instruments,SN74HC151DR,595-SN74HC151DR,Package_SO:SOIC-16_3.9x9.9mm_P1.27mm,,"8:1 mux, SOIC-16"
U4,1,TLV1117LV33DCYR,U,Texas Instruments,TLV1117LV33DCYR,595-TLV1117LV33DCYR,Package_TO_SOT_SMD:SOT-223-3_TabPin2,,"3.3V 1A LDO, ceramic-stable, SOT-223"
U5,1,XIAO ESP32C6,U,Seeed Studio,XIAO ESP32C6,713-113991182,carrier:Seeed_XIAO_ESP32C6_SMD,,"XIAO ESP32C6 module (Seeed SKU 113991182), soldered flat on its 14 castellations (user-supplied; verify Mouser #)"
U6,1,"MP1584EN module, fixed 5V",U,Generic (D-SUN style),MP1584EN mini buck module (fixed 5V output),,carrier:MP1584EN_Module_22x17,,"22x17mm fixed-5V module (no trimmer), user-supplied (Amazon)"
